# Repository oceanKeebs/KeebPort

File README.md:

# KeebPort

Keeb Port is a split keyboard architecture with a central part housing a micro controller and 6 keys (two keys can be replaced with encoders optionally). Right and left part of the split keyboard do not include a micro controller but an IO expander (MCP23017) processing the key activation information and connected via i2c to the central part. The LED control signal is generated by the micro controller and provided via a separate line to both split keyboard parts. Central and split keyboard parts are connected with TRRRS (5-pin). All layouts share the same firmware.

## QMK Firmware source files

### RP2040 QMK firmware source files

<https://github.com/oceanKeebs/qmk_firmware/tree/master/keyboards/oceankeebs/expanded_split_rp_tps43>

## QMK Firmware hex files

### RP2040 QMK firmware hex files

**without via support:**
<https://github.com/oceanKeebs/KeebPort/blob/main/HexFiles/oceankeebs_expanded_split_rp_tps43_default.uf2>

**with via support:**
<https://github.com/oceanKeebs/KeebPort/blob/main/HexFiles/oceankeebs_expanded_split_rp_tps43_via.uf2>

## Keeb Port RP2040

Central part for all split keyboard layouts housing a PGA2040, a TPS65 touch pad and 6 keys (two keys can be replaced with encoders optionally). Needed for all keyboard layouts of this repository.

### PCBs

### STLs

<https://github.com/oceanKeebs/KeebPort/StlFiles/KeebPort_RP2040>

## Kyrious Crab

A SplitKb Kyria inspired split keyboard layout with more aggressive stagger and added num row. Per side 31 keys are available.

### PCBs

## Lucky Albatros

A Lily58 inspired split keyboard layout with 3 additional columns for arrow keys and/or macros. Per side 33 keys are available.

### PCBs

## Template for Custom Layouts

The template can be used a starting point to design compatible custom layouts.

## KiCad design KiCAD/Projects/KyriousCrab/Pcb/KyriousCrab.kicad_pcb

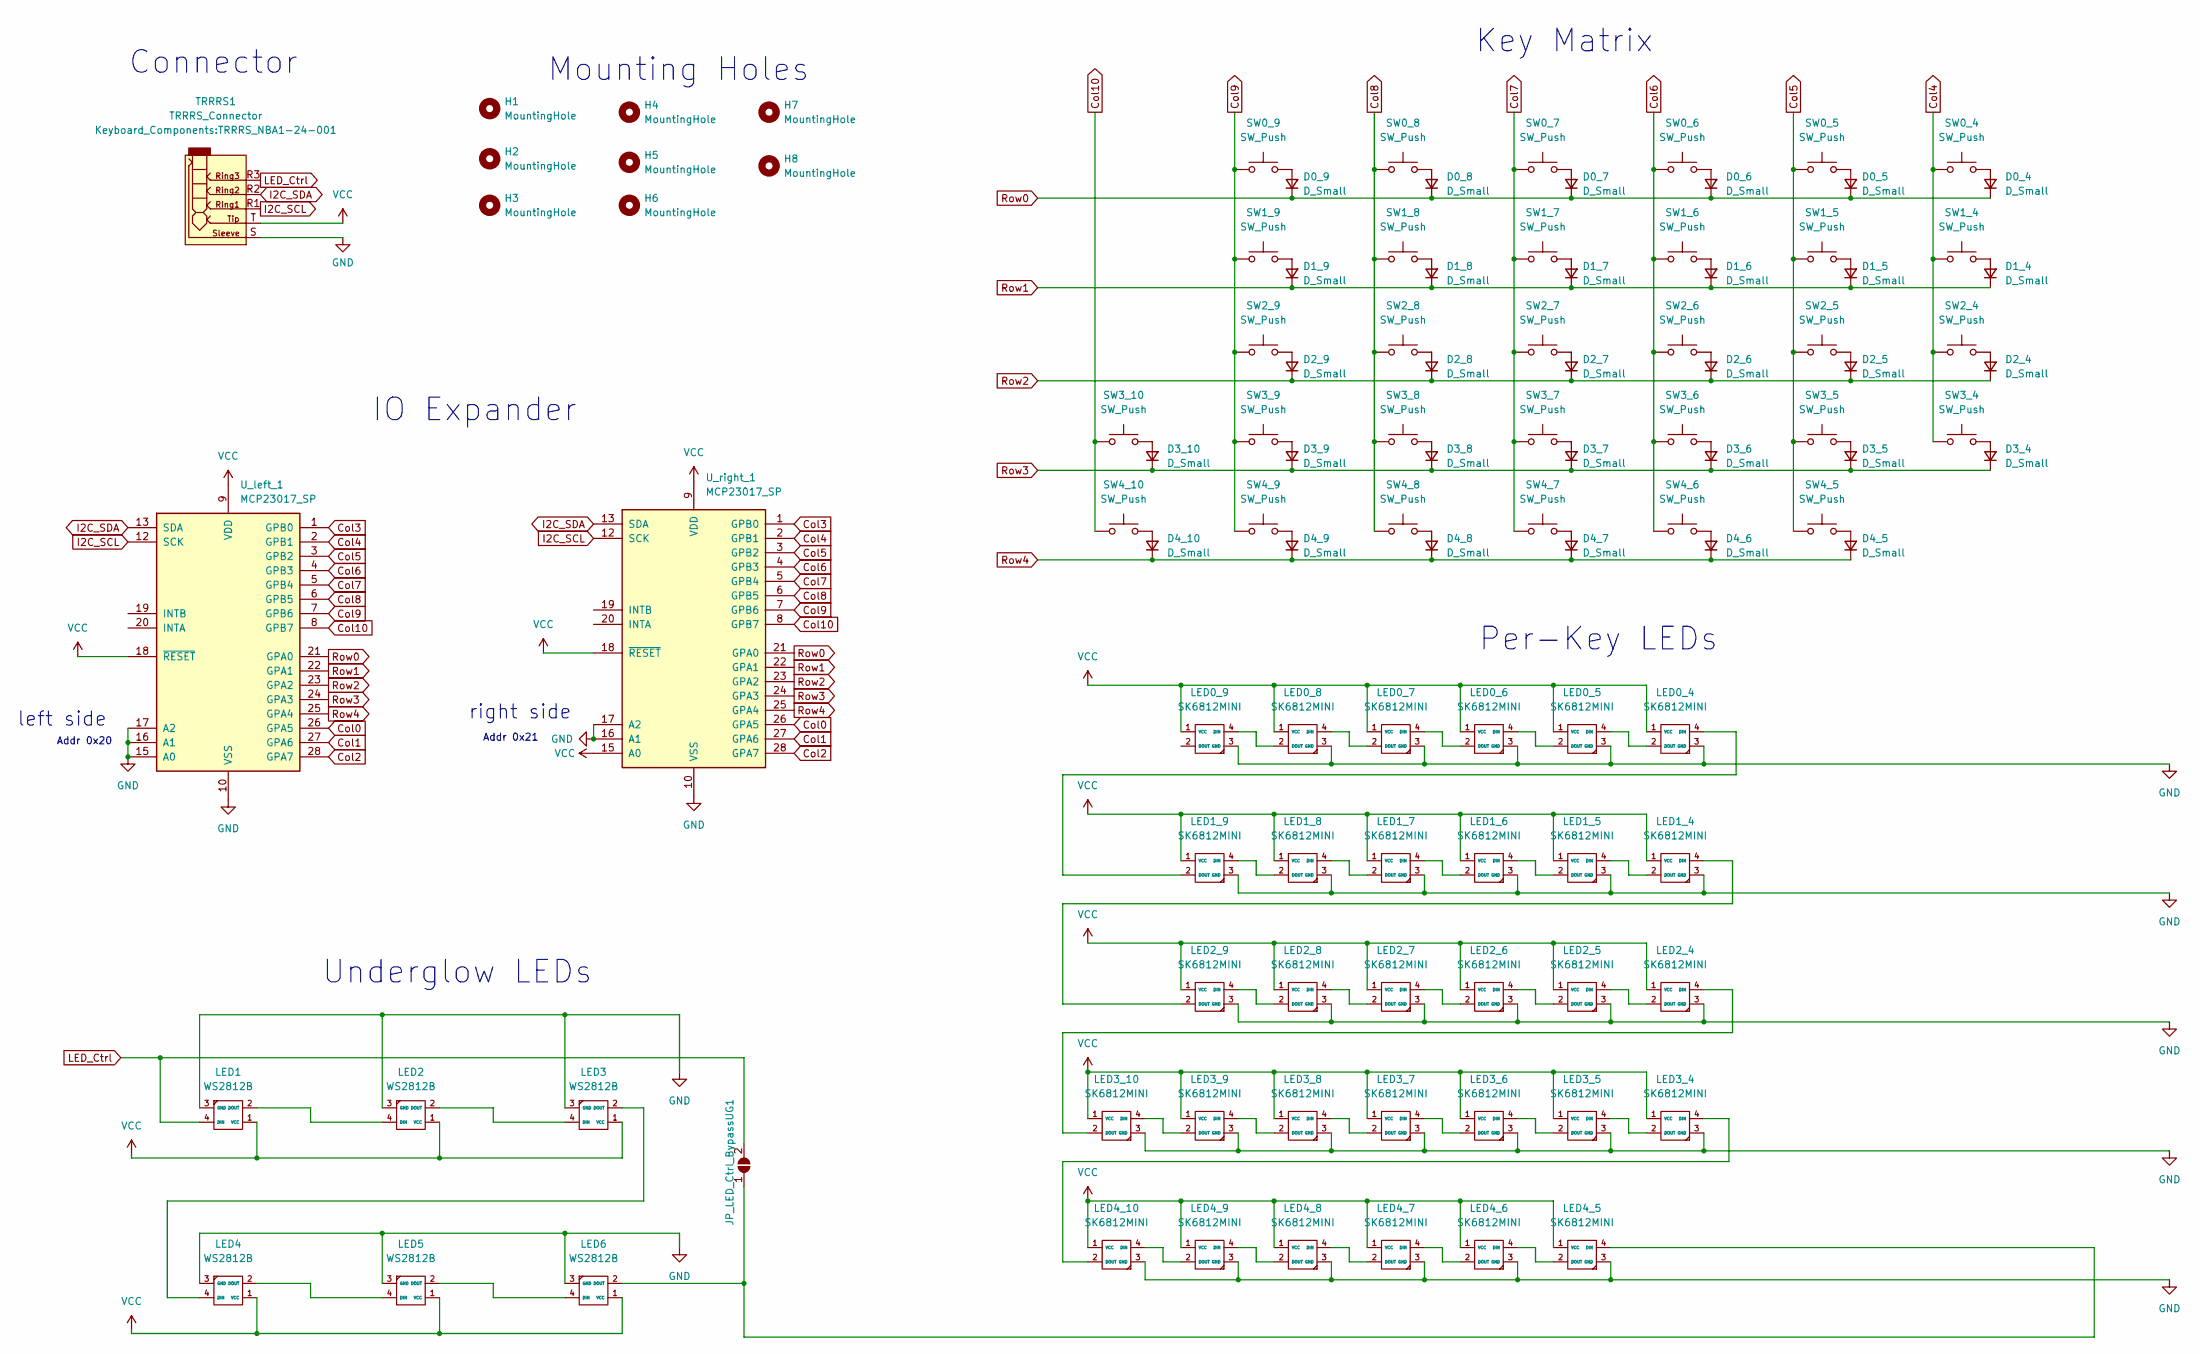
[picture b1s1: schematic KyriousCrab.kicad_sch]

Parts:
D0_4, D0_5, D0_6, D0_7, D0_8, D0_9, D1_4, D1_5, D1_6, D1_7, D1_8, D1_9, D2_4, D2_5, D2_6, D2_7, D2_8, D2_9, D3_4, D3_5, D3_6, D3_7, D3_8, D3_9, D3_10, D4_5, D4_6, D4_7, D4_8, D4_9, D4_10: D_Small; Diode_SMD_Round_Pads
H1, H2, H3, H4, H5, H6, H7, H8: MountingHole; Throughhole_Standoff
JP_LED_Ctrl_BypassUG1: SolderJumper_2_Open; SolderJumper-2_P1.3mm_Open_RoundedPad1.0x1.5mm
LED0_4, LED0_5, LED0_6, LED0_7, LED0_8, LED0_9, LED1_4, LED1_5, LED1_6, LED1_7, LED1_8, LED1_9, LED2_4, LED2_5, LED2_6, LED2_7, LED2_8, LED2_9, LED3_4, LED3_5, LED3_6, LED3_7, LED3_8, LED3_9, LED3_10, LED4_5, LED4_6, LED4_7, LED4_8, LED4_9, LED4_10: SK6812MINI; SK6812MiniE_MX_Addon
LED1, LED2, LED3, LED4, LED5, LED6: WS2812B; WS2812B_doublesided
SW0_4, SW0_5, SW0_6, SW0_7, SW0_8, SW0_9, SW1_4, SW1_5, SW1_6, SW1_7, SW1_8, SW1_9, SW2_4, SW2_5, SW2_6, SW2_7, SW2_8, SW2_9, SW3_4, SW3_5, SW3_6, SW3_7, SW3_8, SW3_9, SW3_10, SW4_5, SW4_6, SW4_7, SW4_8, SW4_9, SW4_10: SW_Push; MX_lss_100U_doubleSided
TRRRS1: TRRRS_Connector; TRRRS_NBA1-24-001
U_left_1: MCP23017_SP; MCP23017_THTasSMD_Singlesided
U_right_1: MCP23017_SP; MCP23017_THTasSMD_Singlesided

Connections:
Col0: U_left_1.26 (GPA5), U_right_1.26 (GPA5)
Col1: U_left_1.27 (GPA6), U_right_1.27 (GPA6)
Col2: U_left_1.28 (GPA7), U_right_1.28 (GPA7)
Col3: U_left_1.1 (GPB0), U_right_1.1 (GPB0)
Col4: SW0_4.1, SW1_4.1, SW2_4.1, SW3_4.1, U_left_1.2 (GPB1), U_right_1.2 (GPB1)
Col5: SW0_5.1, SW1_5.1, SW2_5.1, SW3_5.1, SW4_5.1, U_left_1.3 (GPB2), U_right_1.3 (GPB2)
Col6: SW0_6.1, SW1_6.1, SW2_6.1, SW3_6.1, SW4_6.1, U_left_1.4 (GPB3), U_right_1.4 (GPB3)
Col7: SW0_7.1, SW1_7.1, SW2_7.1, SW3_7.1, SW4_7.1, U_left_1.5 (GPB4), U_right_1.5 (GPB4)
Col8: SW0_8.1, SW1_8.1, SW2_8.1, SW3_8.1, SW4_8.1, U_left_1.6 (GPB5), U_right_1.6 (GPB5)
Col9: SW0_9.1, SW1_9.1, SW2_9.1, SW3_9.1, SW4_9.1, U_left_1.7 (GPB6), U_right_1.7 (GPB6)
Col10: SW3_10.1, SW4_10.1, U_left_1.8 (GPB7), U_right_1.8 (GPB7)
GND: LED0_4.3 (GND), LED0_5.3 (GND), LED0_6.3 (GND), LED0_7.3 (GND), LED0_8.3 (GND), LED0_9.3 (GND), LED1.3 (GND), LED1_4.3 (GND), LED1_5.3 (GND), LED1_6.3 (GND), LED1_7.3 (GND), LED1_8.3 (GND), LED1_9.3 (GND), LED2.3 (GND), LED2_4.3 (GND), LED2_5.3 (GND), LED2_6.3 (GND), LED2_7.3 (GND), LED2_8.3 (GND), LED2_9.3 (GND), LED3.3 (GND), LED3_4.3 (GND), LED3_5.3 (GND), LED3_6.3 (GND), LED3_7.3 (GND), LED3_8.3 (GND), LED3_9.3 (GND), LED3_10.3 (GND), LED4.3 (GND), LED4_5.3 (GND), LED4_6.3 (GND), LED4_7.3 (GND), LED4_8.3 (GND), LED4_9.3 (GND), LED4_10.3 (GND), LED5.3 (GND), LED6.3 (GND), TRRRS1.S, U_left_1.10 (VSS), U_left_1.15 (A0), U_left_1.16 (A1), U_left_1.17 (A2), U_right_1.10 (VSS), U_right_1.16 (A1), U_right_1.17 (A2)
I2C_SCL: TRRRS1.R1, U_left_1.12 (SCK), U_right_1.12 (SCK)
I2C_SDA: TRRRS1.R2, U_left_1.13 (SDA), U_right_1.13 (SDA)
LED_Ctrl: JP_LED_Ctrl_BypassUG1.2 (B), LED1.4 (DIN), TRRRS1.R3
unnamed: D0_4.2 (A), SW0_4.2
unnamed: D0_5.2 (A), SW0_5.2
unnamed: D0_6.2 (A), SW0_6.2
unnamed: D0_7.2 (A), SW0_7.2
unnamed: D0_8.2 (A), SW0_8.2
unnamed: D0_9.2 (A), SW0_9.2
unnamed: D1_4.2 (A), SW1_4.2
unnamed: D1_5.2 (A), SW1_5.2
unnamed: D1_6.2 (A), SW1_6.2
unnamed: D1_7.2 (A), SW1_7.2
unnamed: D1_8.2 (A), SW1_8.2
unnamed: D1_9.2 (A), SW1_9.2
unnamed: D2_4.2 (A), SW2_4.2
unnamed: D2_5.2 (A), SW2_5.2
unnamed: D2_6.2 (A), SW2_6.2
unnamed: D2_7.2 (A), SW2_7.2
unnamed: D2_8.2 (A), SW2_8.2
unnamed: D2_9.2 (A), SW2_9.2
unnamed: D3_4.2 (A), SW3_4.2
unnamed: D3_5.2 (A), SW3_5.2
unnamed: D3_6.2 (A), SW3_6.2
unnamed: D3_7.2 (A), SW3_7.2
unnamed: D3_8.2 (A), SW3_8.2
unnamed: D3_9.2 (A), SW3_9.2
unnamed: D3_10.2 (A), SW3_10.2
unnamed: D4_5.2 (A), SW4_5.2
unnamed: D4_6.2 (A), SW4_6.2
unnamed: D4_7.2 (A), SW4_7.2
unnamed: D4_8.2 (A), SW4_8.2
unnamed: D4_9.2 (A), SW4_9.2
unnamed: D4_10.2 (A), SW4_10.2
unnamed: JP_LED_Ctrl_BypassUG1.1 (A), LED4_5.4 (DIN), LED6.2 (DOUT)
unnamed: LED0_4.2 (DOUT), LED0_5.4 (DIN)
unnamed: LED0_4.4 (DIN), LED1_9.2 (DOUT)
unnamed: LED0_5.2 (DOUT), LED0_6.4 (DIN)
unnamed: LED0_6.2 (DOUT), LED0_7.4 (DIN)
unnamed: LED0_7.2 (DOUT), LED0_8.4 (DIN)
unnamed: LED0_8.2 (DOUT), LED0_9.4 (DIN)
unnamed: LED1.2 (DOUT), LED2.4 (DIN)
unnamed: LED1_4.2 (DOUT), LED1_5.4 (DIN)
unnamed: LED1_4.4 (DIN), LED2_9.2 (DOUT)
unnamed: LED1_5.2 (DOUT), LED1_6.4 (DIN)
unnamed: LED1_6.2 (DOUT), LED1_7.4 (DIN)
unnamed: LED1_7.2 (DOUT), LED1_8.4 (DIN)
unnamed: LED1_8.2 (DOUT), LED1_9.4 (DIN)
unnamed: LED2.2 (DOUT), LED3.4 (DIN)
unnamed: LED2_4.2 (DOUT), LED2_5.4 (DIN)
unnamed: LED2_4.4 (DIN), LED3_10.2 (DOUT)
unnamed: LED2_5.2 (DOUT), LED2_6.4 (DIN)
unnamed: LED2_6.2 (DOUT), LED2_7.4 (DIN)
unnamed: LED2_7.2 (DOUT), LED2_8.4 (DIN)
unnamed: LED2_8.2 (DOUT), LED2_9.4 (DIN)
unnamed: LED3.2 (DOUT), LED4.4 (DIN)
unnamed: LED3_4.2 (DOUT), LED3_5.4 (DIN)
unnamed: LED3_4.4 (DIN), LED4_10.2 (DOUT)
unnamed: LED3_5.2 (DOUT), LED3_6.4 (DIN)
unnamed: LED3_6.2 (DOUT), LED3_7.4 (DIN)
unnamed: LED3_7.2 (DOUT), LED3_8.4 (DIN)
unnamed: LED3_8.2 (DOUT), LED3_9.4 (DIN)
unnamed: LED3_9.2 (DOUT), LED3_10.4 (DIN)
unnamed: LED4.2 (DOUT), LED5.4 (DIN)
unnamed: LED4_5.2 (DOUT), LED4_6.4 (DIN)
unnamed: LED4_6.2 (DOUT), LED4_7.4 (DIN)
unnamed: LED4_7.2 (DOUT), LED4_8.4 (DIN)
unnamed: LED4_8.2 (DOUT), LED4_9.4 (DIN)
unnamed: LED4_9.2 (DOUT), LED4_10.4 (DIN)
unnamed: LED5.2 (DOUT), LED6.4 (DIN)
Row0: D0_4.1 (K), D0_5.1 (K), D0_6.1 (K), D0_7.1 (K), D0_8.1 (K), D0_9.1 (K), U_left_1.21 (GPA0), U_right_1.21 (GPA0)
Row1: D1_4.1 (K), D1_5.1 (K), D1_6.1 (K), D1_7.1 (K), D1_8.1 (K), D1_9.1 (K), U_left_1.22 (GPA1), U_right_1.22 (GPA1)
Row2: D2_4.1 (K), D2_5.1 (K), D2_6.1 (K), D2_7.1 (K), D2_8.1 (K), D2_9.1 (K), U_left_1.23 (GPA2), U_right_1.23 (GPA2)
Row3: D3_4.1 (K), D3_5.1 (K), D3_6.1 (K), D3_7.1 (K), D3_8.1 (K), D3_9.1 (K), D3_10.1 (K), U_left_1.24 (GPA3), U_right_1.24 (GPA3)
Row4: D4_5.1 (K), D4_6.1 (K), D4_7.1 (K), D4_8.1 (K), D4_9.1 (K), D4_10.1 (K), U_left_1.25 (GPA4), U_right_1.25 (GPA4)
VCC: LED0_4.1 (VCC), LED0_5.1 (VCC), LED0_6.1 (VCC), LED0_7.1 (VCC), LED0_8.1 (VCC), LED0_9.1 (VCC), LED1.1 (VCC), LED1_4.1 (VCC), LED1_5.1 (VCC), LED1_6.1 (VCC), LED1_7.1 (VCC), LED1_8.1 (VCC), LED1_9.1 (VCC), LED2.1 (VCC), LED2_4.1 (VCC), LED2_5.1 (VCC), LED2_6.1 (VCC), LED2_7.1 (VCC), LED2_8.1 (VCC), LED2_9.1 (VCC), LED3.1 (VCC), LED3_4.1 (VCC), LED3_5.1 (VCC), LED3_6.1 (VCC), LED3_7.1 (VCC), LED3_8.1 (VCC), LED3_9.1 (VCC), LED3_10.1 (VCC), LED4.1 (VCC), LED4_5.1 (VCC), LED4_6.1 (VCC), LED4_7.1 (VCC), LED4_8.1 (VCC), LED4_9.1 (VCC), LED4_10.1 (VCC), LED5.1 (VCC), LED6.1 (VCC), TRRRS1.T, U_left_1.9 (VDD), U_left_1.18 (~RESET), U_right_1.9 (VDD), U_right_1.15 (A0), U_right_1.18 (~RESET)

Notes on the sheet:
IO Expander
Mounting Holes
Underglow LEDs
Connector
Addr 0x21
right side
left side
Key Matrix
Per-Key LEDs
Addr 0x20

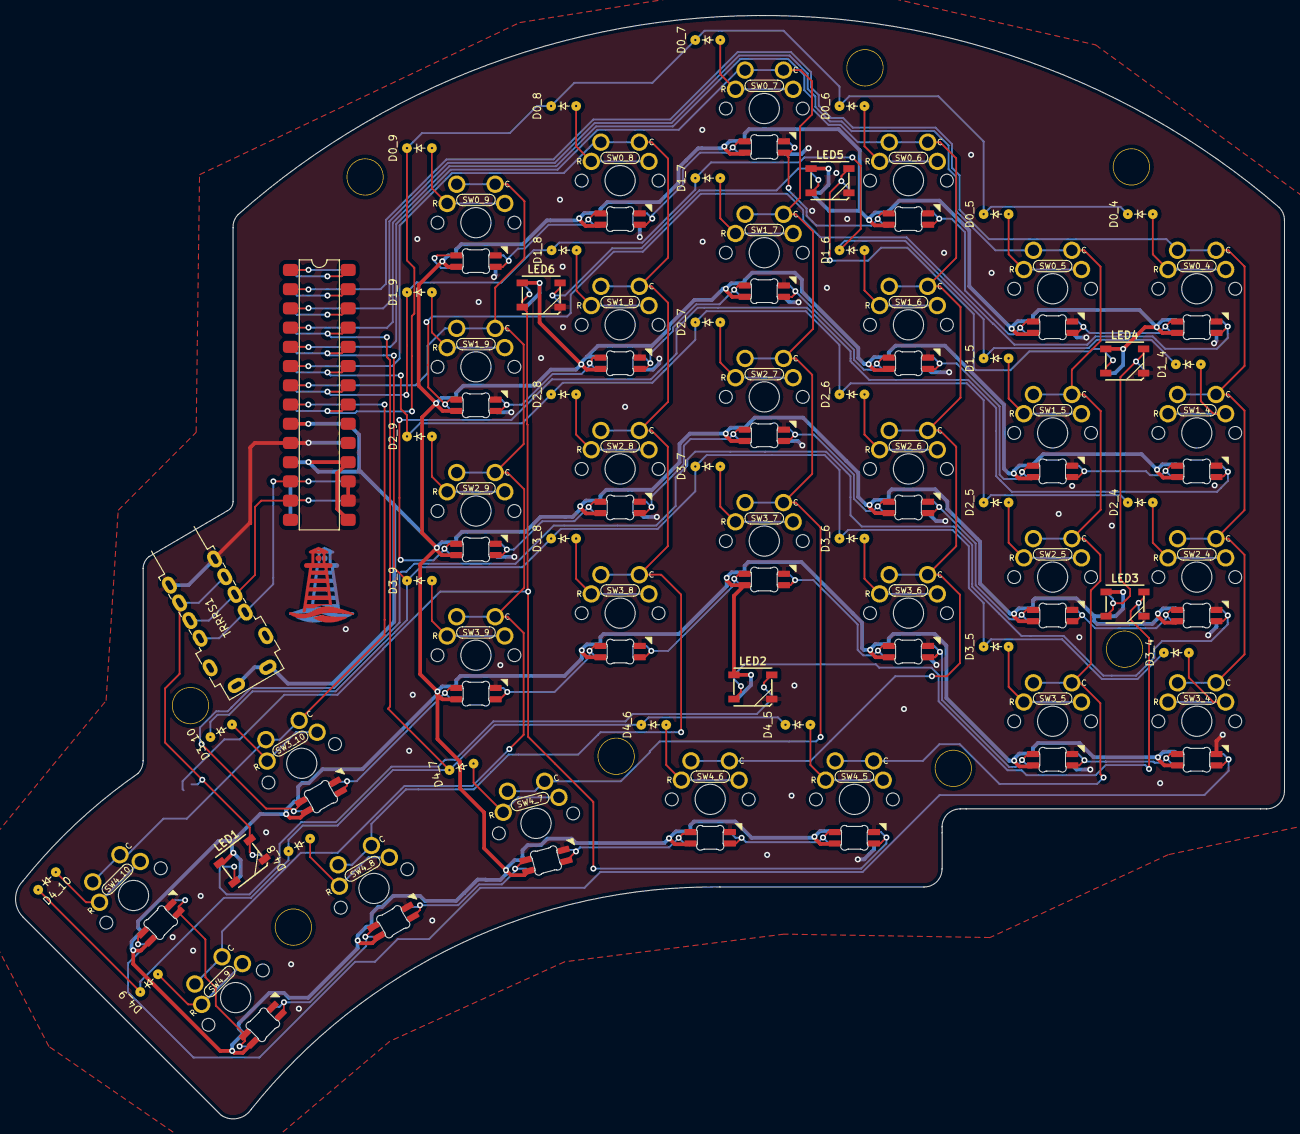
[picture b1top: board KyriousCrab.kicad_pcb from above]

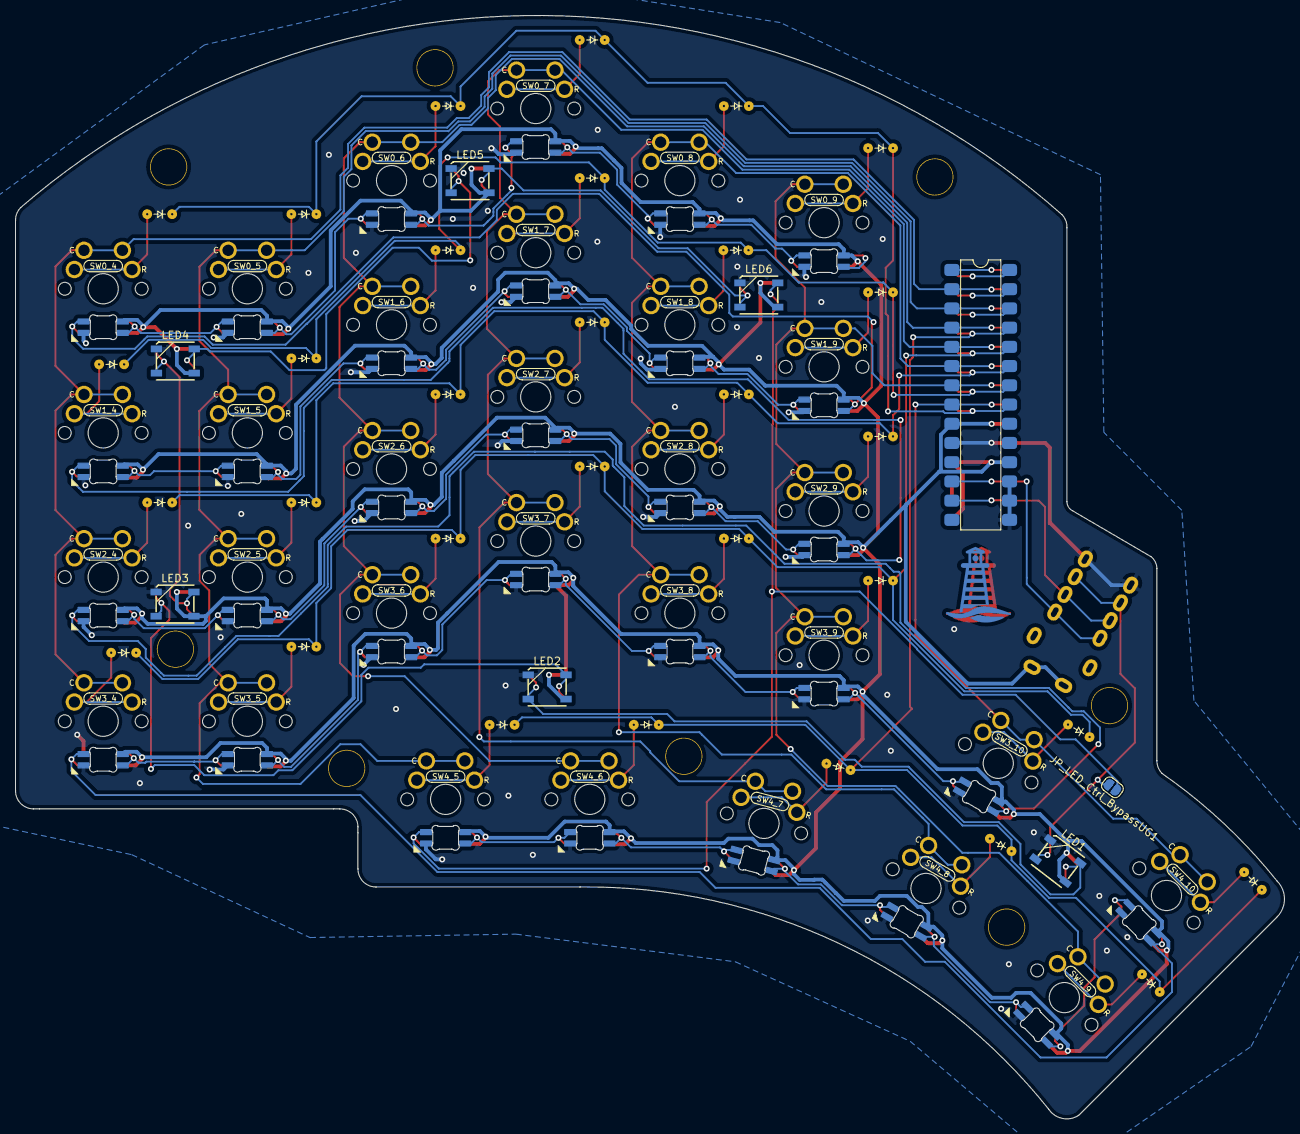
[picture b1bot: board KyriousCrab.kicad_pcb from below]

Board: 2 copper layers, 167.7 x 145.8 mm, 112 parts (2 on the bottom side), 88 nets.

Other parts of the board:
Ref**: Val**; Leuchtturm_10x10

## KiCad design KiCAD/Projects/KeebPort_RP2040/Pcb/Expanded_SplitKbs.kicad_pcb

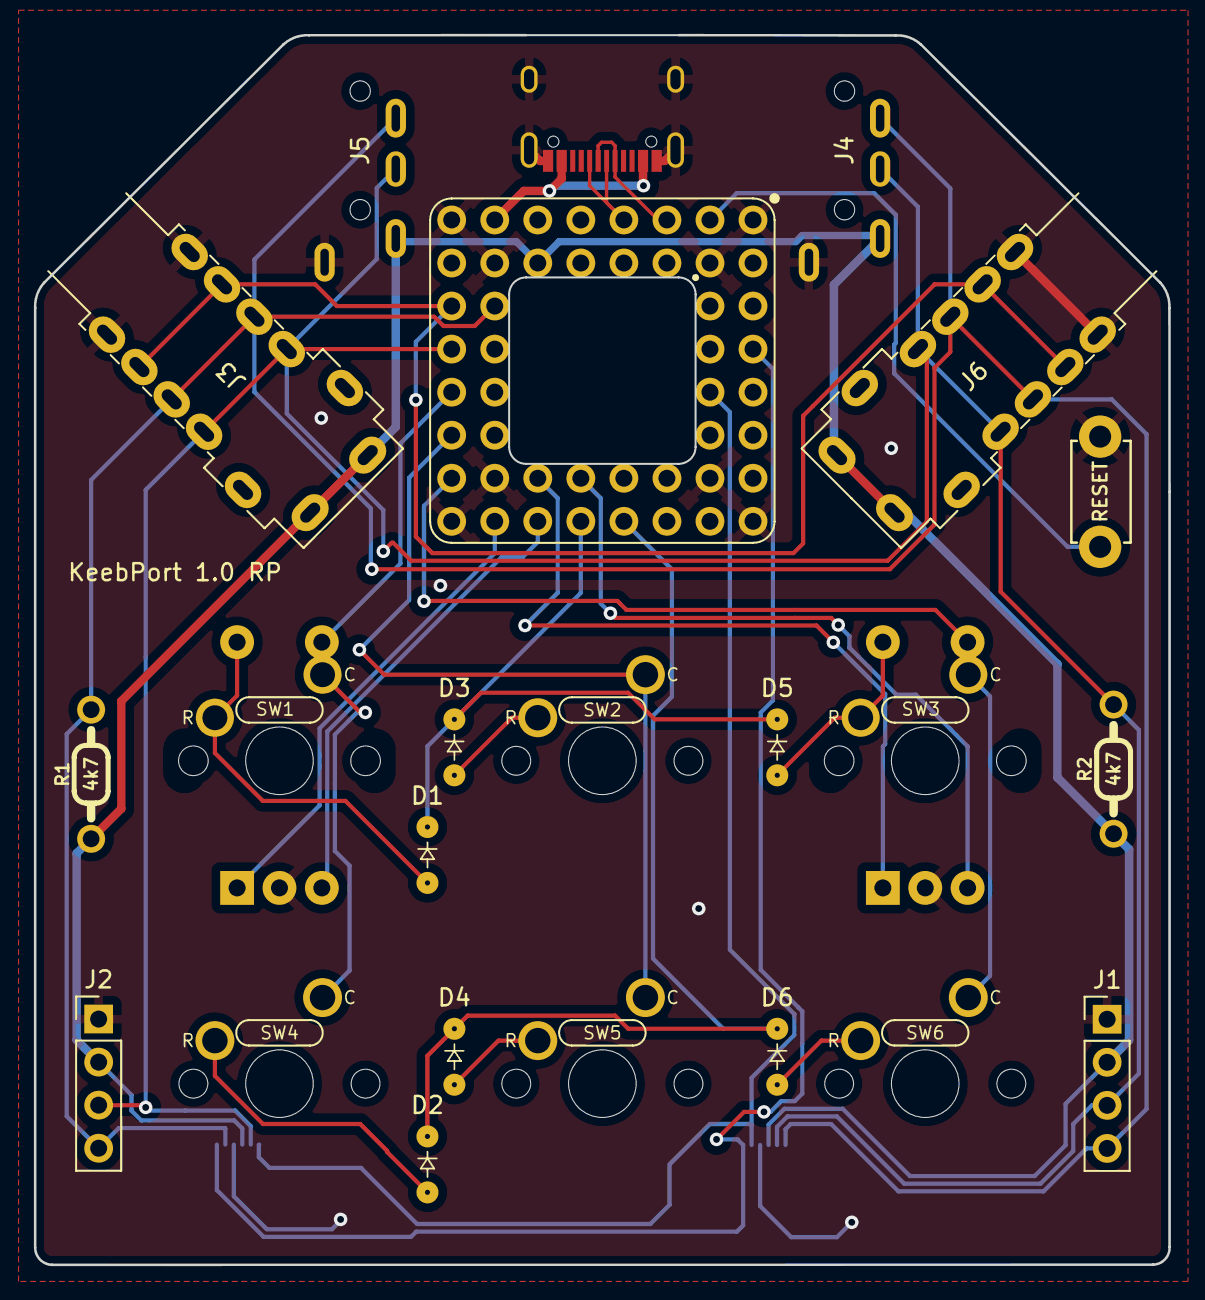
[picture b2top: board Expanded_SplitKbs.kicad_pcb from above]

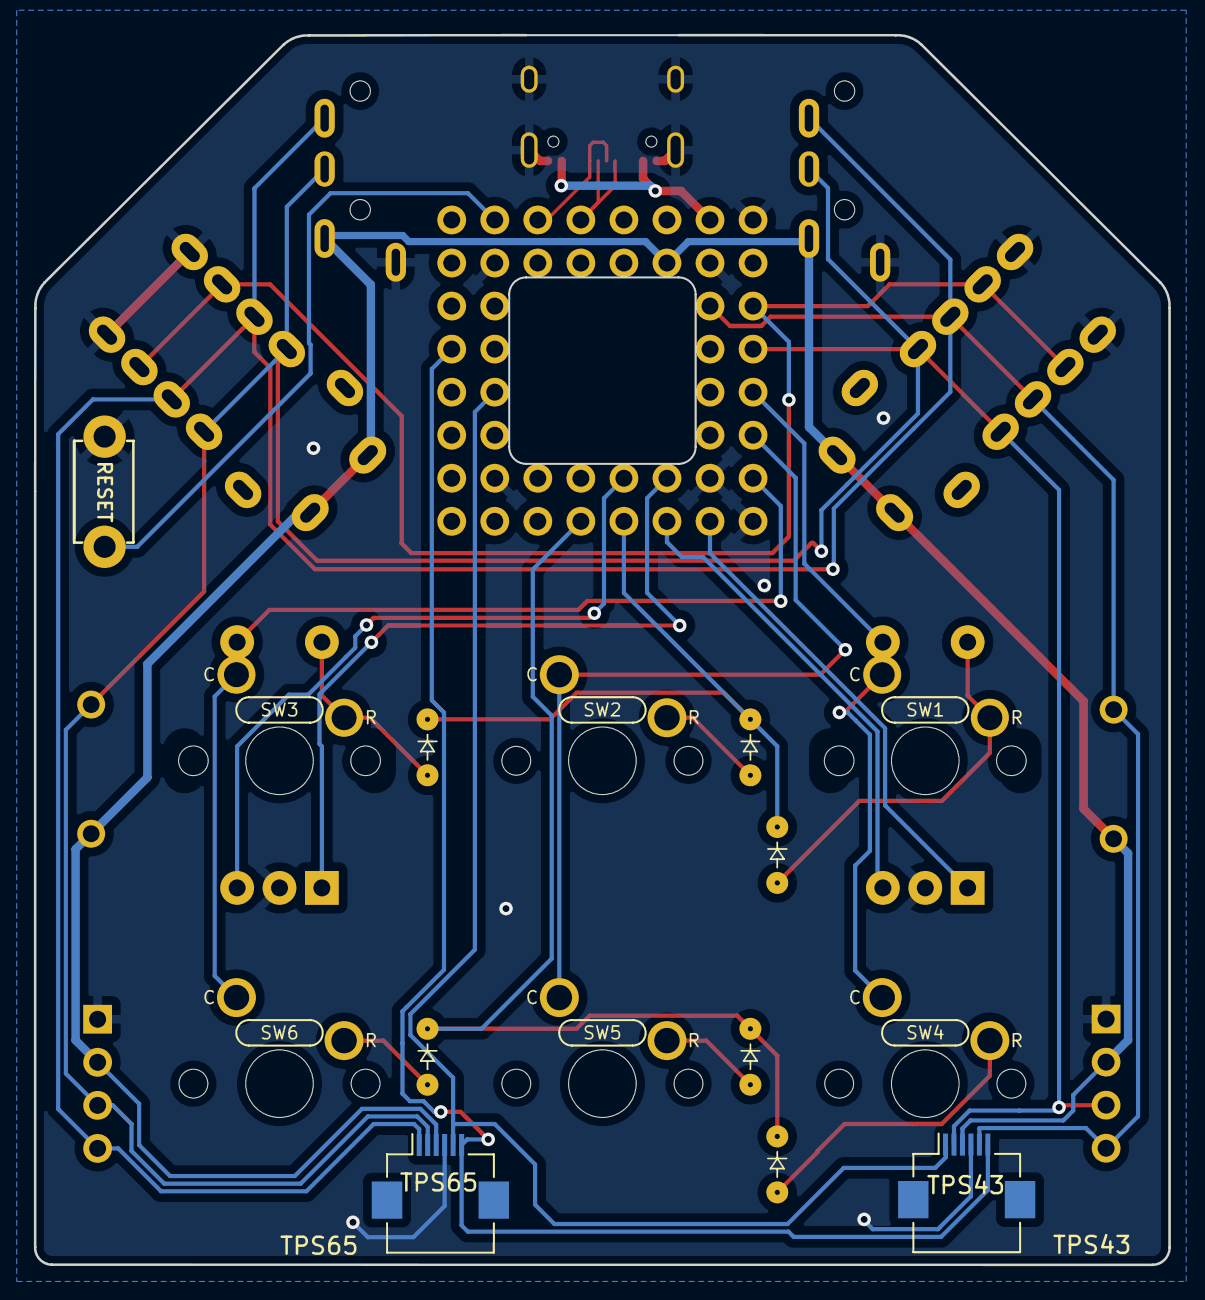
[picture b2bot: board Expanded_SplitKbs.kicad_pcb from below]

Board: 2 copper layers, 66.9 x 72.5 mm, 25 parts (2 on the bottom side), 26 nets.

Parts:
D1, D2, D3, D4, D5, D6: D_Small; Diode_SMD_Round_Pads
J1, J2: Conn_01x04_Female; PinHeader_1x04_P2.54mm_Vertical
J3, J6: TRRRS_Connector; TRRRS_NBA1-24-001
J4, J5: TRRS_Connector; TRRS_PJ-320A
P1: USB_C_Plug; USB_C_C2927037
R1, R2: 4k7; Resistor
SW1, SW3: RotaryEncoder_Switch; MX_lss_100U_Rotary
SW2, SW4, SW5, SW6: SW_Push; MX_lss_100U
SW7: SW_Push; Reset_Switch
TPS43, TPS65: Conn_01x06_Shielded; Hirose_FH12-6S-0.5SH_1x06-1MP_P0.50mm_Horizontal
U1: PGA2040

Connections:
+3V3: J1.2, J2.2, J3.T, J4.T, J5.T, J6.T, R1.1, R2.1, TPS43.3, TPS65.3, U1.B3 (3V3)
Col0: SW1.S2, SW4.1, U1.E1 (GPIO5)
Col1: SW2.1, SW5.1, U1.F1 (GPIO7)
Col2: SW3.S2, SW6.1, U1.G1 (GPIO9)
Enc0_A: SW1.A, U1.H2 (GPIO10)
Enc0_B: SW1.B, U1.H3 (GPIO11)
Enc1_A: SW3.A, U1.G3 (GPIO12)
Enc1_B: SW3.B, U1.G4 (GPIO14)
GND: J1.1, J2.1, J3.S, J4.S, J5.S, J6.S, P1.A1 (GND), P1.A12 (GND), P1.S1 (SHIELD), SW1.C, SW3.C, SW7.1, TPS43.4, TPS65.4, U1.A1 (GND), U1.A8 (GND), U1.B2 (GND), U1.B7 (GND), U1.G2 (GND), U1.G7 (GND), U1.H1 (GND), U1.H8 (GND)
I2C_SCL: J1.3, J2.3, J3.R1, J4.R1, J5.R1, J6.R1, R2.2, TPS43.2, TPS65.2, U1.D1 (GPIO3)
I2C_SDA: J1.4, J2.4, J3.R2, J4.R2, J5.R2, J6.R2, R1.2, TPS43.5, TPS65.1, U1.C2 (GPIO2)
LED_Ctrl: J3.R3, J6.R3, U1.C1 (GPIO1)
NRST: TPS43.1, TPS65.5, U1.E7 (GPIO24)
unnamed: D1.2 (A), SW1.S1
unnamed: D2.2 (A), SW4.2
unnamed: D3.2 (A), SW2.2
unnamed: D4.2 (A), SW5.2
unnamed: D5.2 (A), SW3.S1
unnamed: D6.2 (A), SW6.2
unnamed: SW7.2, U1.A7 (BOOTSEL)
RDY: TPS43.6, TPS65.6, U1.D8 (GPIO25)
Row0: D1.1 (K), D3.1 (K), D5.1 (K), U1.H4 (GPIO13)
Row1: D2.1 (K), D4.1 (K), D6.1 (K), U1.H5 (GPIO15)
USB_D+: P1.A6 (D+), P1.B6 (D+), U1.A5 (USB_DP)
USB_D-: P1.A7 (D-), P1.B7 (D-), U1.A6 (USB_DM)
VBUS: P1.A4 (VBUS), P1.A9 (VBUS), U1.A2 (VBUS)

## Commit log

2024-04-02 Update LICENSE
2024-04-02 Added KiCAD info, pictures and hex files
2024-04-02 removed typos and lint warnings in README.md
2024-04-03 Added render and stl files
2024-04-03 corrected version of used TPS in KeebPort RP2040
